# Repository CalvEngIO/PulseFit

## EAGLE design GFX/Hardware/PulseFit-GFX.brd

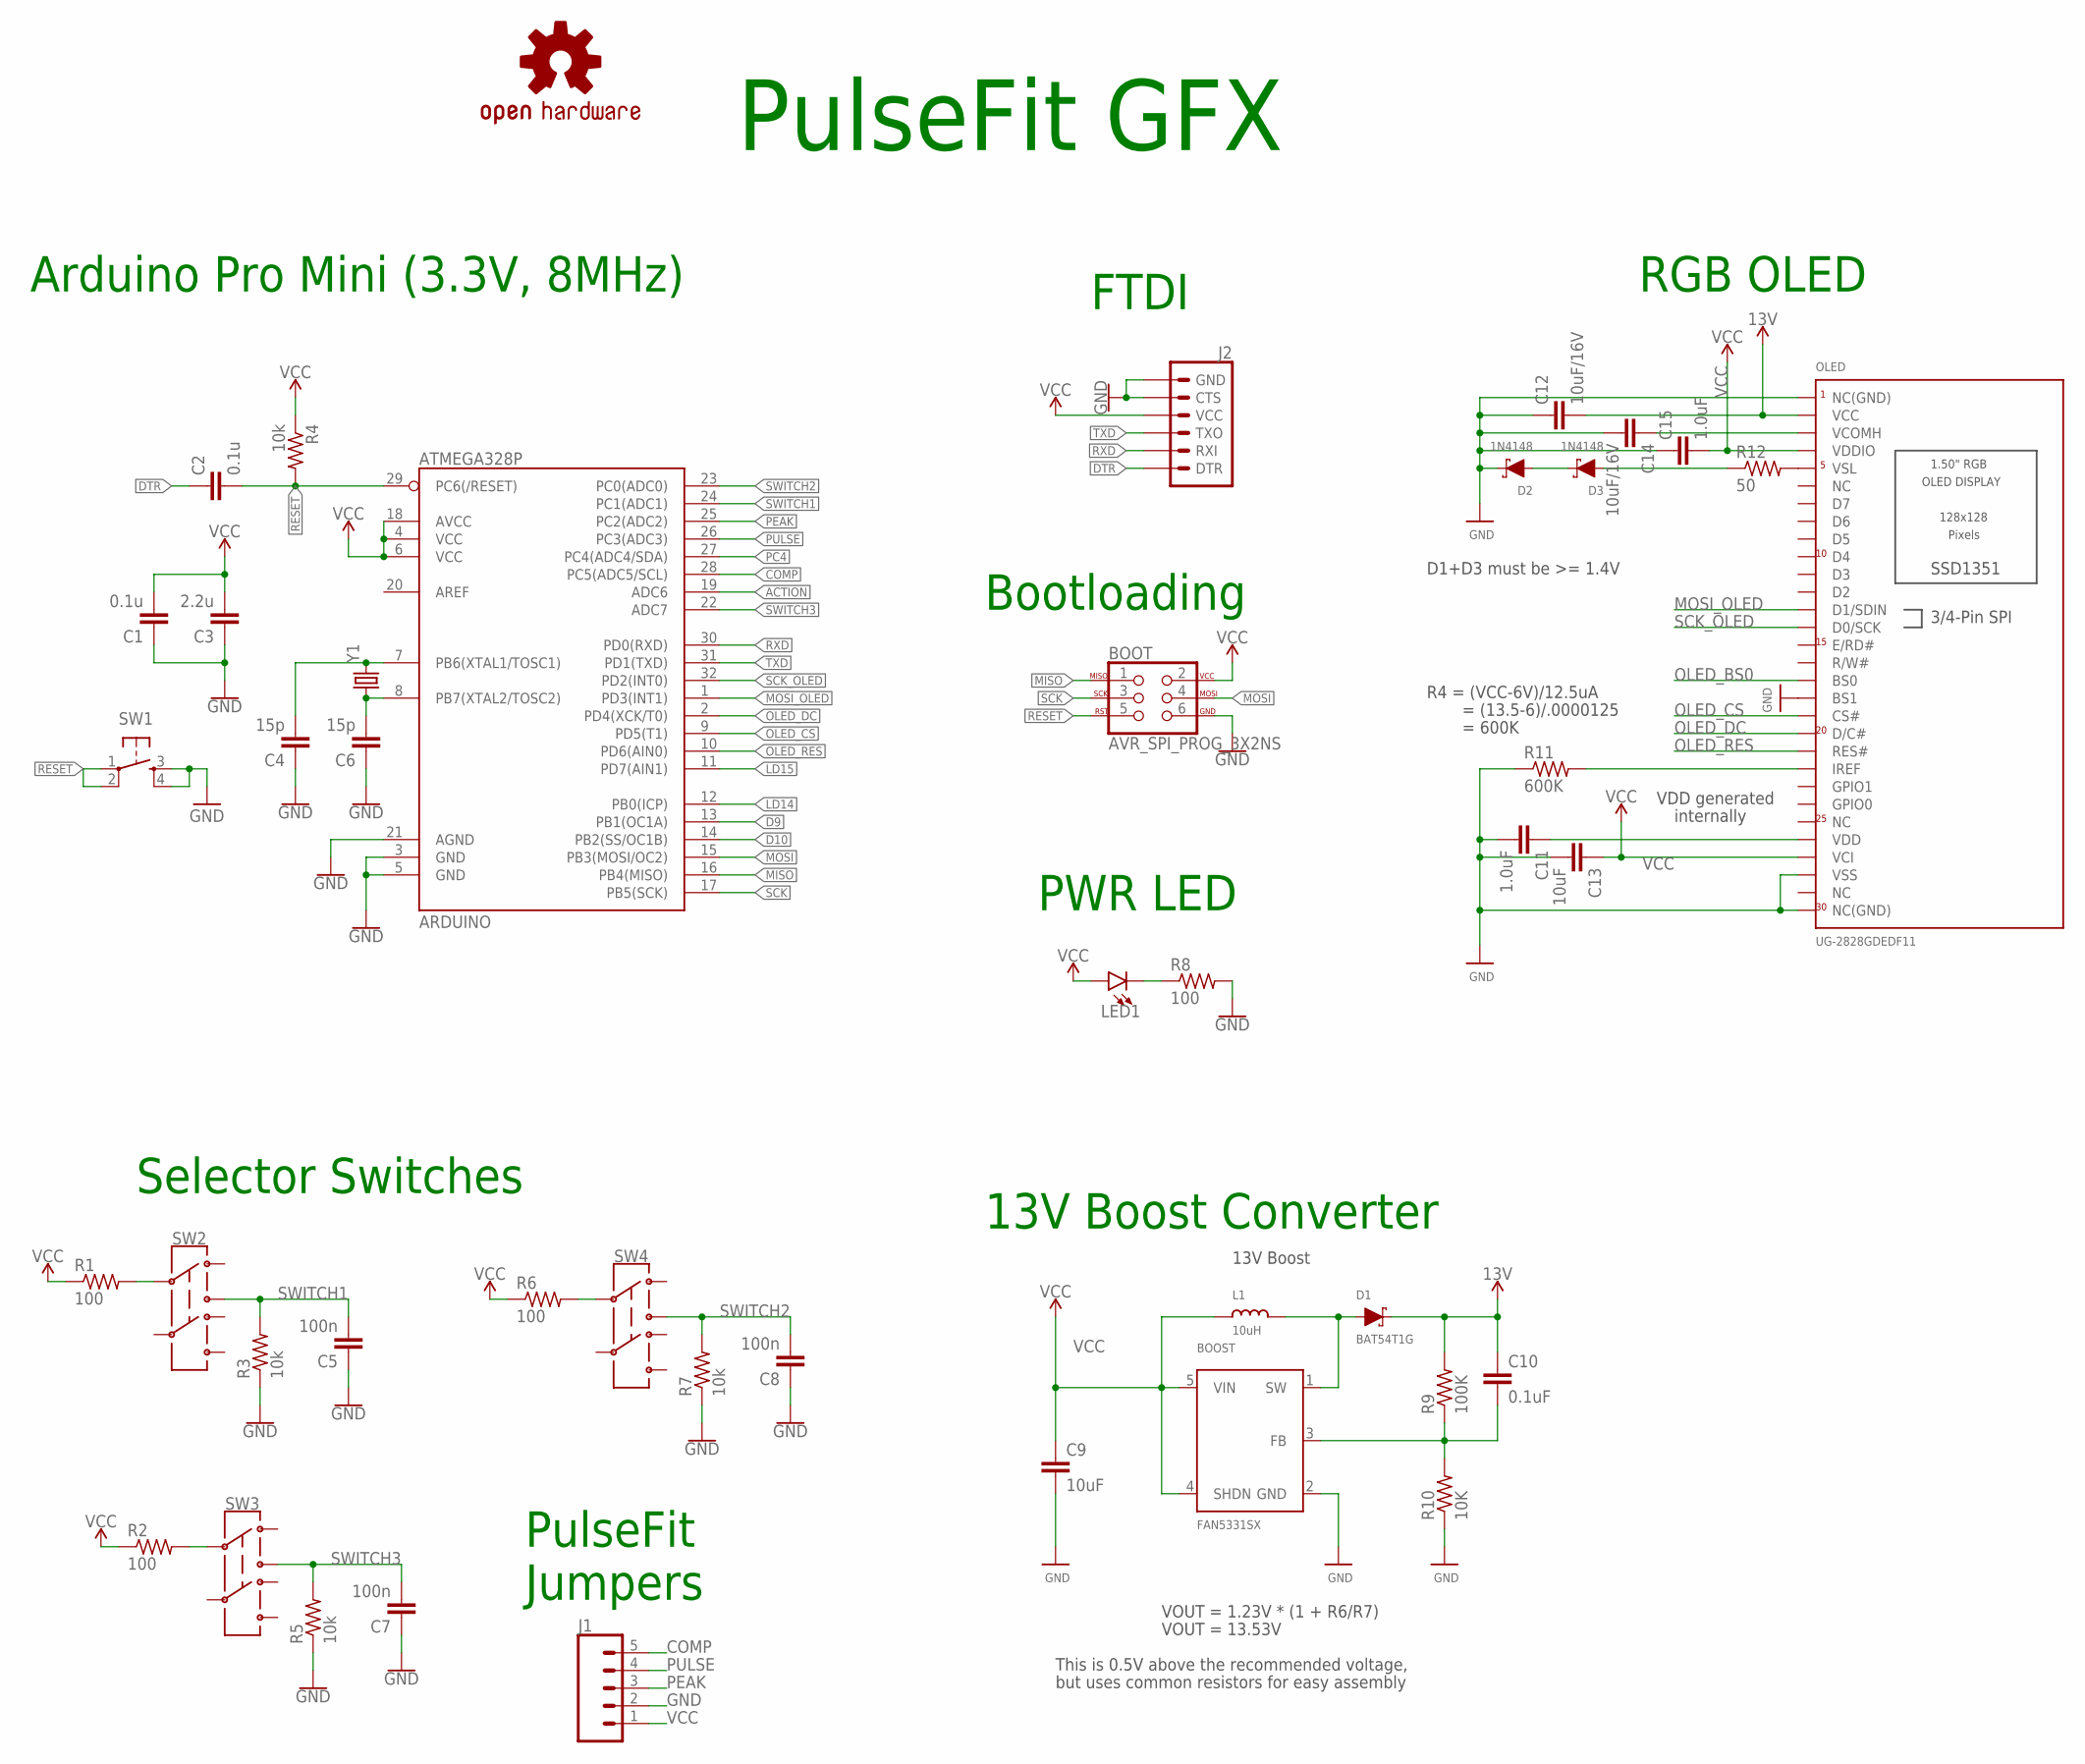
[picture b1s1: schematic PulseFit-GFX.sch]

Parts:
ARDUINO: ATMEGA328P; TQFP32-08
BOOST: FAN5331SX; SOT23-5@1
BOOT: AVR_SPI_PROG_3X2NS; 2X3-NS
C1, C2: 0.1u; C0603
C3: 2.2u; C0805
C4, C6: 15p; C0603
C5, C7, C8: 100n; C0603
C9, C13: 10uF; C0805
C10: 0.1uF; C0603
C11, C15: 1.0uF; C0603
C12, C14: 10uF/16V; C0805
D1: BAT54T1G; USC
D2, D3: 1N4148; USC
J1: CONN_05; 1X05
J2: 6_PIN_SERIAL_TARGETSILK; 6_PIN_SERIAL_TARGET_SIDE_W_SILK
L1: 10uH; INDUCTOR_1007
LED1: LED5MM; LED_5MM
LOGO1: CALVENGIO_HANDLEHANDLE.05; CALVENGIO_HANDLE.05
LOGO2: OSHW-LOGOS; OSHW-LOGO-S
LOGO3: REVISION.A; REV.A
OLED: UG-2828GDEDF11; FPC_XF2M-3015-1A
R1, R2, R6, R8: 100; R0603
R3, R4, R5, R7: 10k; R0603
R9: 100K; R0603
R10: 10K; R0603
R11: 600K; R0603
R12: 50; R0603
SW1: SPST-PTS830GG140; BUTTON-GULLWING
SW2, SW3, SW4: SWITCH.JS202011JXQNUPWARDS; SWITCH.00
Y1: CRYSTAL-CA-310; CA-301

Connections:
13V: C10.1, C12.2, D1.- (C), OLED.P$29 (VCC), R9.2
ACTION: ARDUINO.19 (ADC6)
COMP: ARDUINO.28 (PC5(ADC5/SCL)), J1.5
D9: ARDUINO.13 (PB1(OC1A))
D10: ARDUINO.14 (PB2(SS/OC1B))
DTR: C2.1, J2.P$1 (DTR)
GND: ARDUINO.3 (GND), ARDUINO.5 (GND), ARDUINO.21 (AGND), BOOST.2 (GND), BOOT.6, C1.1, C3.1, C4.1, C5.1, C6.1, C7.1, C8.1, C9.2, C11.2, C12.1, C13.2, C14.2, C15.1, D2.- (C), J1.2, J2.P$5 (CTS), J2.P$6 (GND), OLED.P$1 (NC(GND)), OLED.P$3 (VSS), OLED.P$13 (BS1), OLED.P$30 (NC(GND)), R3.1, R5.1, R7.1, R8.2, R10.1, R11.1, SW1.3, SW1.4
IREF: OLED.P$9 (IREF), R11.2
LD14: ARDUINO.12 (PB0(ICP))
LD15: ARDUINO.11 (PD7(AIN1))
MISO: ARDUINO.16 (PB4(MISO)), BOOT.1
MOSI: ARDUINO.15 (PB3(MOSI/OC2)), BOOT.4
MOSI_OLED: ARDUINO.1 (PD3(INT1)), OLED.P$18 (D1/SDIN)
unnamed: ARDUINO.7 (PB6(XTAL1/TOSC1)), C4.2, Y1.2
unnamed: ARDUINO.8 (PB7(XTAL2/TOSC2)), C6.2, Y1.1
unnamed: LED1.K (C), R8.1
unnamed: C11.1, OLED.P$5 (VDD)
unnamed: BOOST.1 (SW), D1.+ (A), L1.P$2 (2)
unnamed: OLED.P$26 (VSL), R12.2
unnamed: D3.+ (A), R12.1
unnamed: BOOST.3 (FB), C10.2, R9.1, R10.2
unnamed: R6.2, SW4.2
unnamed: R2.2, SW3.2
unnamed: R1.2, SW2.2
unnamed: D2.+ (A), D3.- (C)
OLED_BS0: OLED.P$14 (BS0)
OLED_CS: ARDUINO.9 (PD5(T1)), OLED.P$12 (CS#)
OLED_DC: ARDUINO.2 (PD4(XCK/T0)), OLED.P$11 (D/C#)
OLED_RES: ARDUINO.10 (PD6(AIN0)), OLED.P$10 (RES#)
PC4: ARDUINO.27 (PC4(ADC4/SDA))
PEAK: ARDUINO.25 (PC2(ADC2)), J1.3
PULSE: ARDUINO.26 (PC3(ADC3)), J1.4
RESET: ARDUINO.29 (PC6(/RESET)), BOOT.5, C2.2, R4.2, SW1.1, SW1.2
RXD: ARDUINO.30 (PD0(RXD)), J2.P$3 (RXI)
SCK: ARDUINO.17 (PB5(SCK)), BOOT.3
SCK_OLED: ARDUINO.32 (PD2(INT0)), OLED.P$17 (D0/SCK)
SWITCH1: ARDUINO.24 (PC1(ADC1)), C5.2, R3.2, SW2.3
SWITCH2: ARDUINO.23 (PC0(ADC0)), C8.2, R7.2, SW4.3
SWITCH3: ARDUINO.22 (ADC7), C7.2, R5.2, SW3.3
TXD: ARDUINO.31 (PD1(TXD)), J2.P$2 (TXO)
VCC: ARDUINO.4 (VCC), ARDUINO.6 (VCC), ARDUINO.18 (AVCC), BOOST.4 (SHDN), BOOST.5 (VIN), BOOT.2, C1.2, C3.2, C9.1, C13.1, C15.2, J1.1, J2.P$4 (VCC), L1.P$1 (1), LED1.A, OLED.P$4 (VCI), OLED.P$27 (VDDIO), R1.1, R2.1, R4.1, R6.1
VCOMH1: C14.1, OLED.P$28 (VCOMH)

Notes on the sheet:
FTDI
Bootloading
VOUT = 1.23V * (1 + R6/R7)
VOUT = 13.53V
This is 0.5V above the recommended voltage,
but uses common resistors for easy assembly
13V Boost
R4 = (VCC-6V)/12.5uA
= (13.5-6)/.0000125
= 600K
D1+D3 must be >= 1.4V
VDD generated
internally
Arduino Pro Mini (3.3V, 8MHz)
RGB OLED
13V Boost Converter
Selector Switches
PulseFit Jumpers
PWR LED
PulseFit GFX

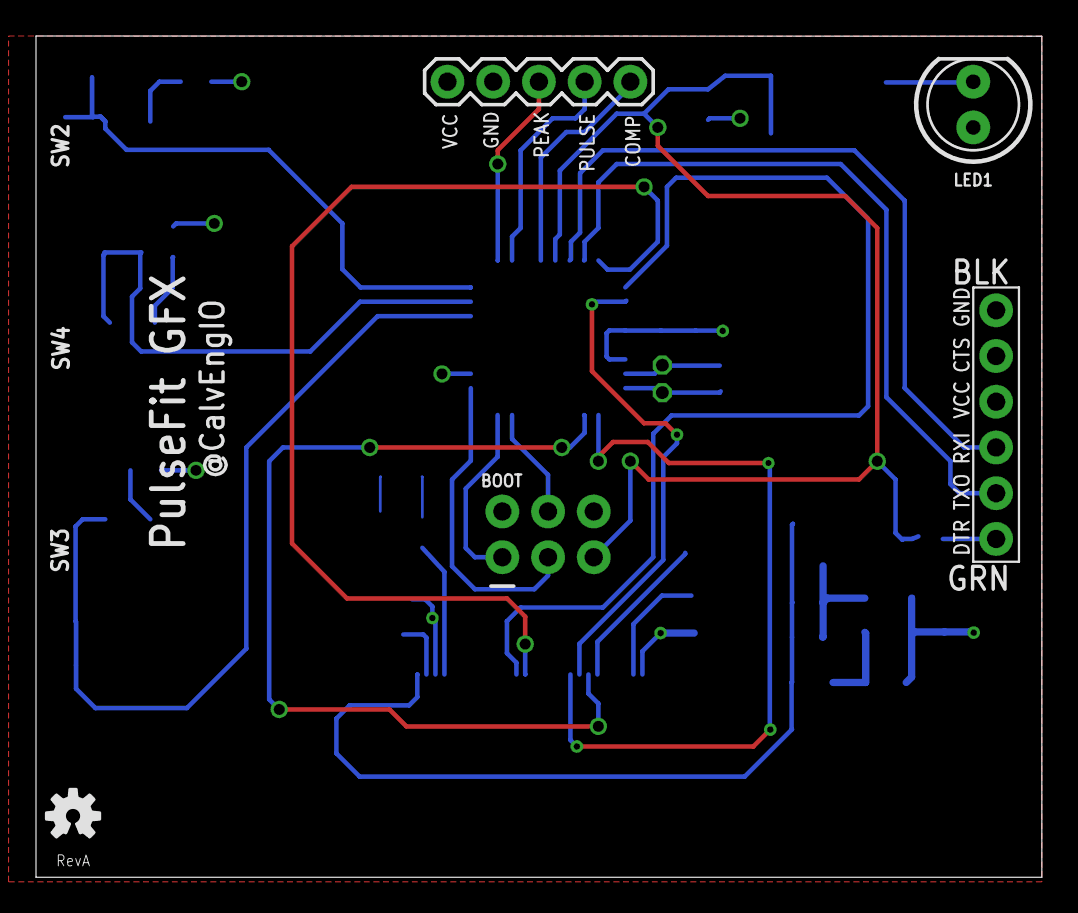
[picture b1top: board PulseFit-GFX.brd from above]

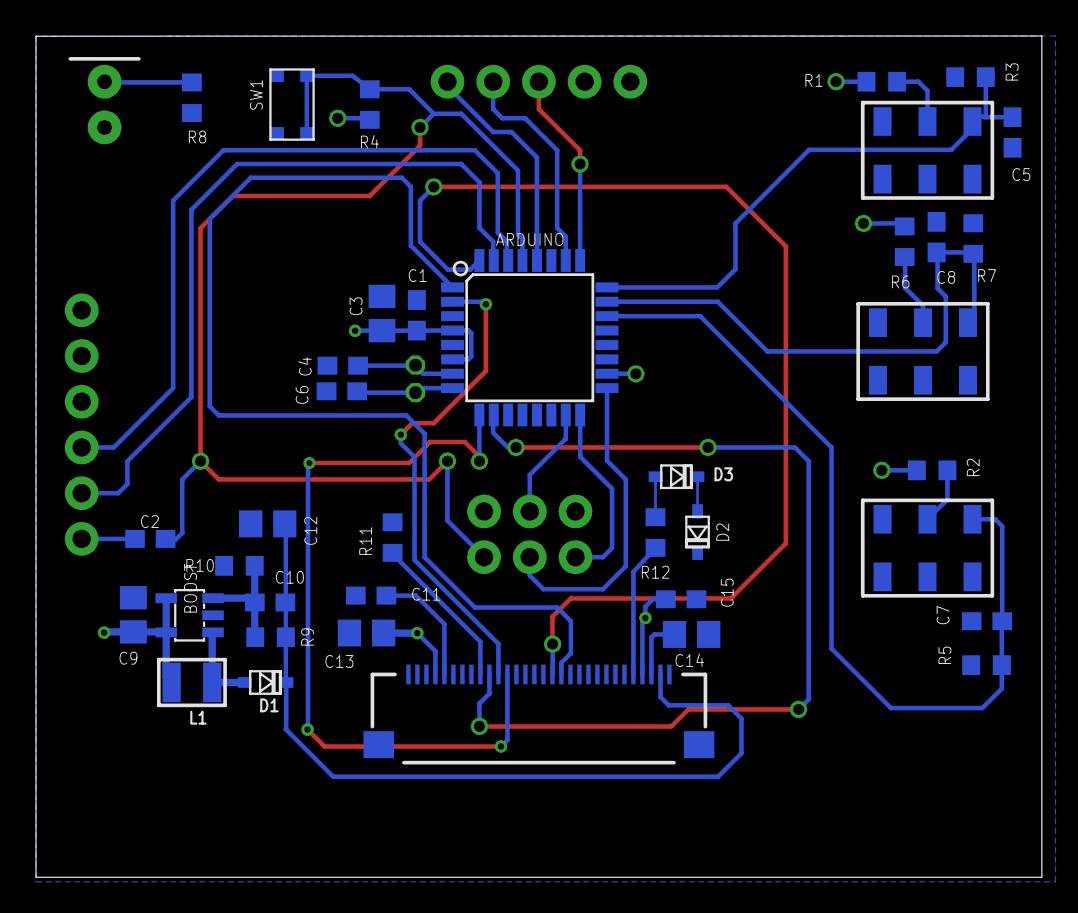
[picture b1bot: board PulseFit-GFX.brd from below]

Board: 2 copper layers, 55.9 x 46.7 mm, 46 parts (38 on the bottom side), 35 nets.

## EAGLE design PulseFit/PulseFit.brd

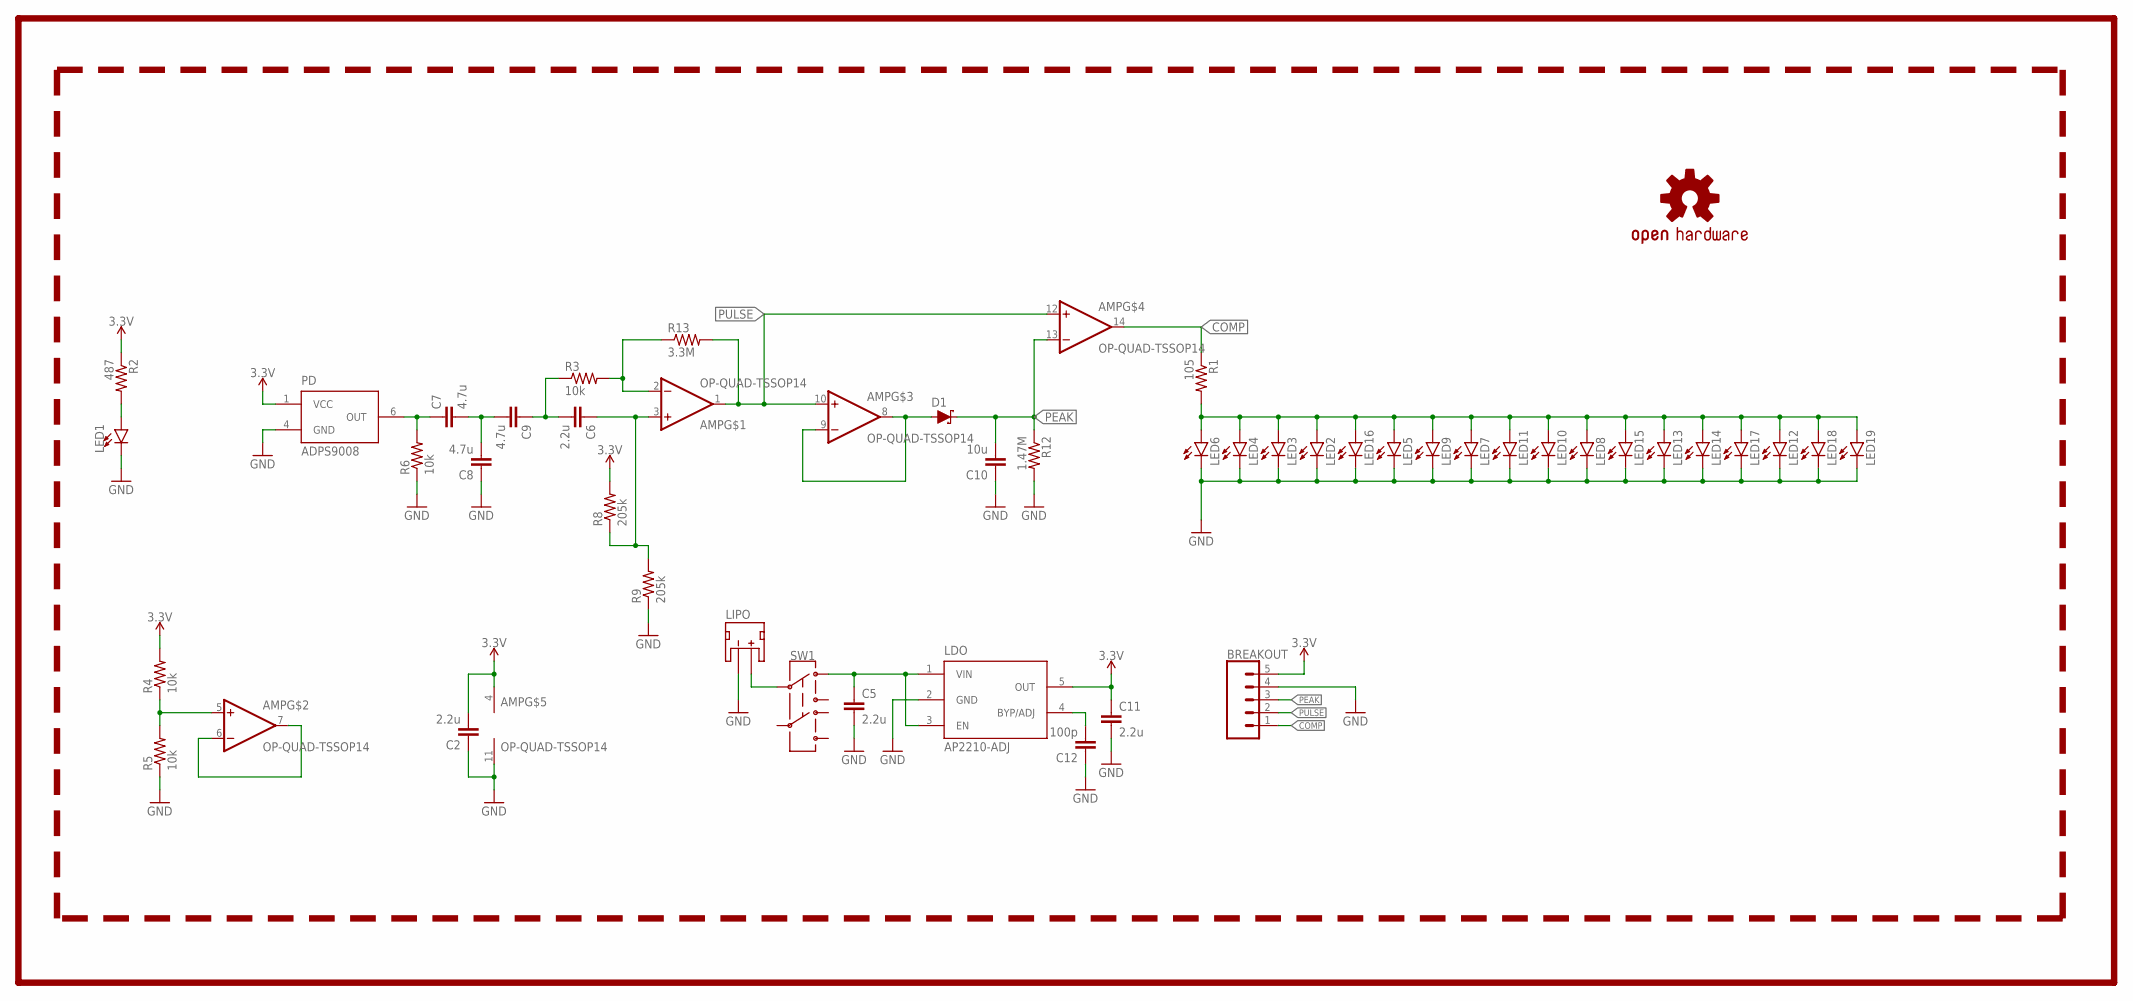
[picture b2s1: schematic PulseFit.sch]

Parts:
AMP: OP-QUAD-TSSOP14; TSSOP14
BREAKOUT: CONN_05NO_SILK; 1X05_NO_SILK
C2: 2.2u; C0402
C5, C6, C11: 2.2u; C0603
C7, C8, C9: 4.7u; C0603
C10: 10u; C0805
C12: 100p; C0402
D1: SCHOTTKY-USC; USC
LDO: AP2210-ADJ; SOT23-5
LED1: LEDZ-BEND; 2-SMD.Z-BEND
LED2, LED3, LED4, LED5, LED6, LED7, LED8, LED9, LED10, LED11, LED12, LED13, LED14, LED15, LED16, LED17, LED18, LED19: LED5MM
LIPO: JST_2MM_MALE; JST-2-SMD
LOGO1: OSHW-LOGOS; OSHW-LOGO-S
PD: ADPS9008; 6-PIN.CHIPLED
R1: 105; R0402
R2: 487; R0402
R3, R4, R5, R6: 10k; R0402
R8, R9: 205k; R0402
R12: 1.47M; R0402
R13: 3.3M; R0402
SW1: SWITCH.JS202011JCQN; SWITCH.00
U$1: CALVENGIO_HANDLEHANDLE.05; CALVENGIO_HANDLE.05
U$2: REVISION.F; REV.F

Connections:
3.3V: AMP.4 (V+), BREAKOUT.5, C2.2, C11.1, LDO.5 (OUT), PD.1 (VCC), R2.1, R4.2, R8.2
ANODE: LED2.A, LED3.A, LED4.A, LED5.A, LED6.A, LED7.A, LED8.A, LED9.A, LED10.A, LED11.A, LED12.A, LED13.A, LED14.A, LED15.A, LED16.A, LED17.A, LED18.A, LED19.A, R1.2
COMP: AMP.14 (OUT), BREAKOUT.1, R1.1
GND: AMP.11 (V-), BREAKOUT.4, C2.1, C5.2, C8.1, C10.1, C11.2, C12.1, LDO.2 (GND), LED1.- (C), LED2.K (C), LED3.K (C), LED4.K (C), LED5.K (C), LED6.K (C), LED7.K (C), LED8.K (C), LED9.K (C), LED10.K (C), LED11.K (C), LED12.K (C), LED13.K (C), LED14.K (C), LED15.K (C), LED16.K (C), LED17.K (C), LED18.K (C), LED19.K (C), LIPO.1 (-), PD.4 (GND), R5.1, R6.1, R9.1, R12.2
unnamed: AMP.5 (+IN), R4.1, R5.2
unnamed: AMP.6 (-IN), AMP.7 (OUT)
unnamed: C12.2, LDO.4 (BYP/ADJ)
unnamed: LIPO.2 (+), SW1.2
unnamed: LED1.+ (A), R2.2
unnamed: AMP.8 (OUT), AMP.9 (-IN), D1.+ (A)
unnamed: C5.1, LDO.1 (VIN), LDO.3 (EN), SW1.1
unnamed: C7.2, C8.2, C9.2
unnamed: C6.2, C9.1, R3.1
unnamed: AMP.2 (-IN), R3.2, R13.1
unnamed: AMP.3 (+IN), C6.1, R8.1, R9.2
unnamed: C7.1, PD.6 (OUT), R6.2
PEAK: AMP.13 (-IN), BREAKOUT.3, C10.2, D1.- (C), R12.1
PULSE: AMP.1 (OUT), AMP.10 (+IN), AMP.12 (+IN), BREAKOUT.2, R13.2

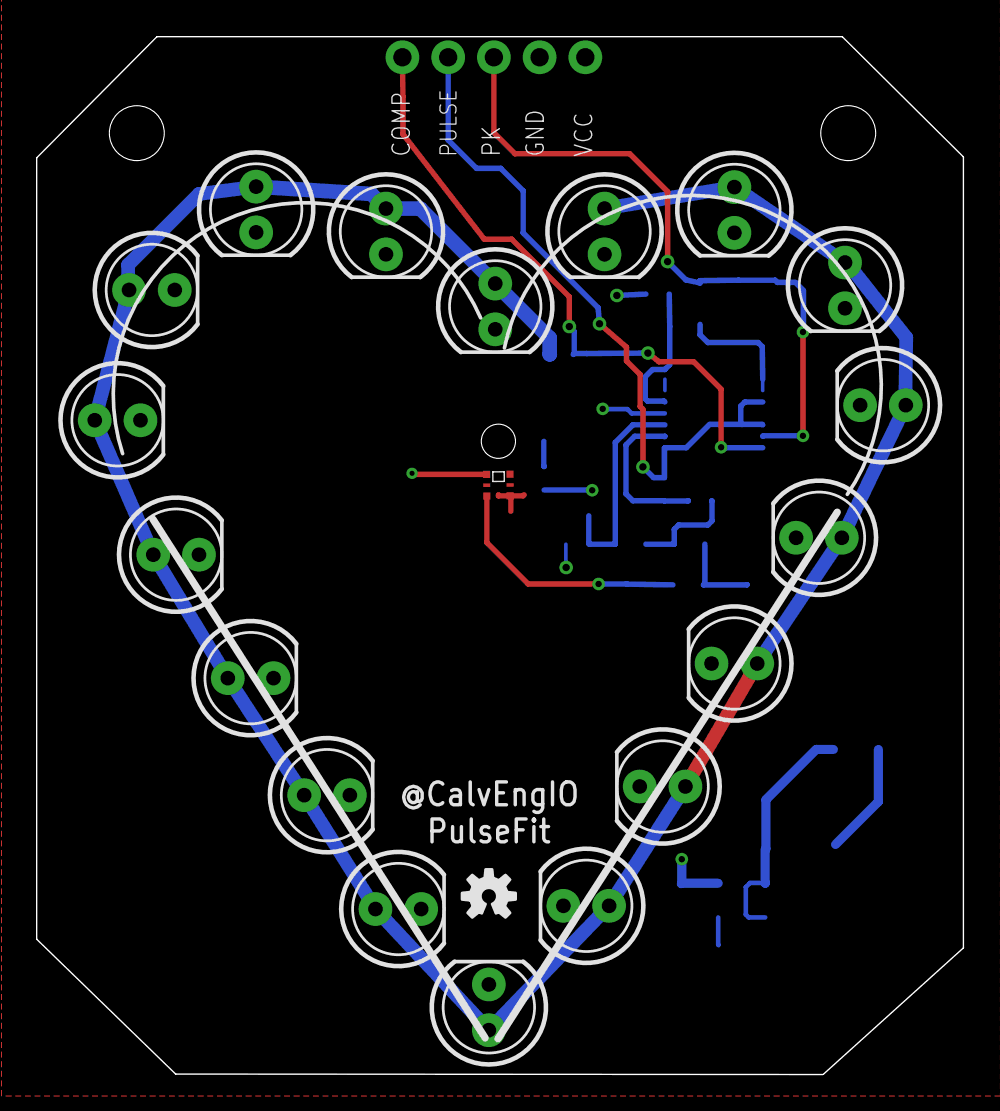
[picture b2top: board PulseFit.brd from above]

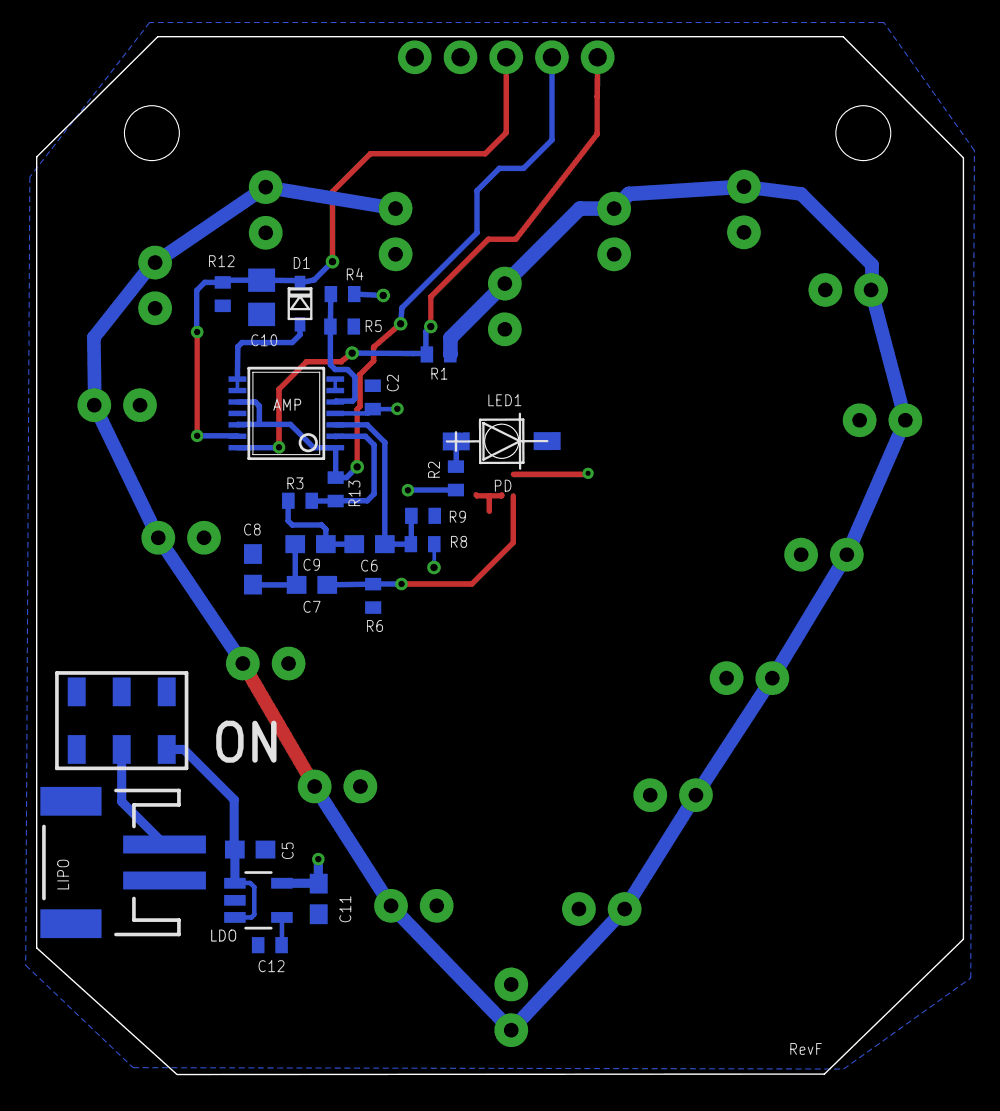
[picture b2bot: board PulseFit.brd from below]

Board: 2 copper layers, 51.5 x 57.7 mm, 48 parts (26 on the bottom side), 18 nets.

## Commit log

2017-06-06 Create LICENSE-Hardware
2017-06-06 Rename LICENSE-Hardware to LICENSE-Hardware.txt
2017-06-07 initial commit with first iteration of the schematic
2017-06-13 first itteration of pulsefit
2017-06-22 next board
2017-07-10 deleted extra bypass capacitors and changed their values a bit
2017-07-10 slight updates moving capacitors around and such
2017-08-13 these are the most up to date files, but new versions soon to come
2017-08-13 most up to date files, but more to come
2021-04-02 updated .gitignore
2021-04-02 reorganized and regrouped repo
2021-04-03 documenting small change before bigger change

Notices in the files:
Hardware/PulseFit.sch:
Creative Commons License
parts and their libraries:
SparkFun-DigitalIC: Licensing: Creative Commons ShareAlike 4.0 International - https://creativecommons.org/licenses/by-sa/4.0
